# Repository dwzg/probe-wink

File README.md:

# probe-wink

Wink and alternation mod for the pop-up headlamps of the 1989–92 Ford Probe.
Each headlamp gets a small sealed module that plugs in between the factory
retractor plug and the retractor through a Y-adapter. A relay in the module
swaps the retractor's UP and DOWN command lines, so one lamp can go down while
the other stays up (a wink), or the two can flip in turn. With the relay off,
the car behaves exactly as stock. The LH module talks to a phone and a BLE
remote; the RH module follows it over an authenticated ESP-NOW link. Power
comes from the retractor's own feed; no wires go into the cabin.

## Status

| Part              | State                                                   |
|-------------------|---------------------------------------------------------|
| PCB (rev C)       | designed, ERC/DRC and layout checks pass; not yet built |
| Housing (rev C)   | designed and checked on the model; not yet printed      |
| Firmware          | logic unit-tested on the host; runs on an ESP32 devkit (boot, radio, BLE, phone pairing); not yet run on the module |
| Android app       | built with home-screen widgets; unit tests and lint pass; not yet run on a phone |
| On the car        | nothing tested yet                                      |

## How it works, in short

Both retractors hang on the same two command wires from the headlamp switch.
That is why the lamps always move together. Crossing the two wires for one
retractor sends that lamp the opposite way. Details:
[docs/how-it-works.md](docs/how-it-works.md).

## Documentation

- [How it works](docs/how-it-works.md)
- [Installation](docs/installation.md)
- [Using it](docs/using.md)
- [Building](docs/building.md)
- [Testing](docs/testing.md)
- [Design notes](docs/design-notes.md)

## Repository

| Path            | Contents                                                     |
|-----------------|--------------------------------------------------------------|
| `docs/`         | documentation and diagrams                                   |
| `pcb/`          | KiCad project, generated from Python (`schematic.py`, `check.py`, `board.py`, `fab.py`, `export_enclosure.py`); [README](pcb/README.md) |
| `enclosure/`    | 3D-printable housing in build123d (`housing.py`, `check.py`, `render.py`); current STEP/STL in `enclosure/models/` |
| `firmware/`     | Rust on ESP-IDF for the ESP32-C3; [README](firmware/README.md) |
| `android/`      | Android app with home-screen widgets; [README](android/README.md) |
| `tools/hw-design/` | submodule: [hw-design](https://github.com/dwzg/hw-design), the KiCad and build123d library used by `pcb/` and `enclosure/` |
| `Makefile`      | one target per part                                          |

## Quick start

The board and housing generators use the [hw-design](https://github.com/dwzg/hw-design)
library as a submodule. Clone with `git clone --recurse-submodules`, or run
`git submodule update --init` in an existing clone.

```sh
make pcb         # schematic -> ERC/netlist check -> board (route, DRC, layout checks) -> JLCPCB files
make enclosure   # board geometry -> housing STEP/STL -> enclosure checks -> renders
make firmware    # module firmware; needs WINK_BLE_PASSKEY (couple the modules in the app)
make devkit      # the same firmware for an ESP32 DEVKITV1 test bench
make android     # Android app, debug APK
make test        # firmware logic tests + Android unit tests
```

What each target needs (KiCad 10, Freerouting, a Python venv for build123d,
the Rust toolchain): [docs/building.md](docs/building.md).

## Safety

- The module switches the command lines of the headlamp retractors. With the
  relay off, the wiring is stock: at power-up, in reset, in sleep, and without a
  module. Unplugging the Y-adapter restores the original wiring completely.
- Each module's 12 V tap runs through a 1 A fuse in the adapter. Motor power
  never passes through the module.
- The retractor linkage is strong enough to hurt. Disconnect the battery before
  working on it, and keep hands clear whenever it has power.
- Winking or flashing headlamps while driving may be illegal where you live.
  Treat both modes as parked-car features. The modules cannot see whether the
  car is moving.
- This is a hobby project, not yet tested on a car. Use it at your own risk.

## Licence

- **Software** (`firmware/`, `android/`, and the generator scripts in
  `pcb/` and `enclosure/`): [MIT](LICENSE).
- **Hardware design** (the KiCad files in `pcb/`, the housing models built by
  `enclosure/`): [CERN-OHL-P-2.0](LICENSE-HARDWARE), the permissive CERN Open
  Hardware Licence. Source location: <https://github.com/dwzg/probe-wink>.

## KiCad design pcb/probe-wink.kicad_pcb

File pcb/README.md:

# PCB: probe-wink module (rev C)

One module per headlamp. 46 × 40 mm, 2 layers, ESP32-C3-WROOM-02 (or -02U with an
external antenna: same pads) with the antenna overhanging the right edge, TE IM06GR
swap relay, LMR16006X buck from the retractor's own 12 V feed. The module connects
through a 6-wire lead to a Y-adapter between the factory retractor plug and socket;
motor current stays in the adapter.

The KiCad files are **generated**. Edit the Python sources, not the `.kicad_*` files:

| File | Role |
|---|---|
| `schematic.py` | Parts, values, LCSC numbers, nets → `probe-wink.kicad_sch`, `intended_netlist.json` |
| `check.py` | ERC, netlist export, compare against the declared nets |
| `board.py` | Outline, placement, hand-routed power paths, keep-outs, Freerouting, pours, stitching, DRC, layout checks |
| `fab.py` | JLCPCB Gerber/drill zip, BOM, CPL, assembly drawings → `build/fab/` |
| `export_enclosure.py` | Board STEP and geometry JSON for the housing → `../enclosure/build/` |
| `lib/probe-wink.pretty` | Project footprints (back-side pogo pads for J2) |
| `../tools/hw-design/` | Submodule: the generic generator library [hw-design](https://github.com/dwzg/hw-design) (`hwdesign.kicad`) |

## Rebuild

```sh
make pcb                      # from the repository root: the first four steps below

cd pcb
python3 schematic.py          # schematic + lib tables
python3 check.py              # ERC + netlist (board.py reads build/probe-wink.net)
python3 board.py              # about 90 s; add --no-route while iterating on placement
python3 fab.py                # build/fab/
python3 export_enclosure.py   # ../enclosure/build/board.json + probe-wink-board.step
```

Needs KiCad 10 (`pcbnew` Python module, `kicad-cli`), Freerouting on `PATH`,
`rsvg-convert` for the PNG renders.

`board.py` runs the Freerouting strategies in parallel and caches each result
under `build/route-cache/` by a hash of the routing input. A rerun with unchanged
placement (silkscreen, rules) takes about 10 s.

Status at last generation: ERC 0, schematic overlap check 0, netlist matches the
declared nets. DRC 0 errors, 0 unconnected; one warning, the WROOM-02 footprint
differing from the library copy (intentional). 18 of 18 layout checks pass.

## Layout

DRC checks clearances. It does not check whether parts that must be close are close.
`board.py` therefore hand-places and hand-routes the paths that decide whether the
buck and the module behave, and the autorouter only does the rest:

- **Buck** (TI LMR16006 §11.1/11.2): U1 rotated so VIN sits above Cin (C2). The
  catch diode D3 sits beside Cin, so the Cin–switch–diode loop closes on top copper.
  L1 is on the SW side, the output caps are at the L1/D3 junction, and the ground
  ties into the plane at the output caps. The FB divider is at the FB pin, away
  from L1. The back copper under the buck is a solid plane (track keep-out).
- **Module supply:** 100 nF then 10 µF straight above pin 1, fed along the top edge.
  EN jogs left over the unused pins 3/4 to its RC and pull-up.
- **Module body:** no tracks on either layer under the module; GND stitching allowed.
- **Bottom plane:** no tracks under the input stage, FB divider and buck (keep-out
  116–131.6 × 102–122). The FB divider's ground runs on top to the IC ground; its 3V3
  comes from the top-edge rail and crosses under the 12 V link by a 4 mm hop at the edge.
- **Programming:** J2 (EN, 3V3, BOOT, GND) is a 2 × 2 pogo pad set on the back right
  behind the module's top row, so its traces stay local. USB D−/D+ pads are behind the
  bottom row.
- **Harness lines** (HARN_*, RET_*) have their own net class: 0.4 mm, 0.5 mm clearance
  (coupled bursts, no TVS on these lines).
- After routing, extra GND vias go next to the sense and ADC grounds (`via_near`), and
  autorouter leftovers that lead nowhere are removed (`prune_dangling`).
- **Sense buffers:** two compact cells (divider, filter cap, zener on a short gate
  bus, MOSFET, pull-up), placed next to the harness pads.

After routing, `board.py` measures the routed copper between pad pairs
(`hwdesign.kicad.board.path_length`) and fails loudly if a limit is exceeded:

| Path | Rev B | Rev C | Limit |
|---|---|---|---|
| SW: U1 → L1 | 14.7 mm, 2 vias | 6.1 mm | 8 mm, top only |
| SW: U1 → D3 | 11.8 mm, 2 vias | 3.6 mm | 4 mm |
| FB: U1 → R9 | 7.2 mm, 2 vias | 1.7 mm | 3 mm |
| 3V3: module pin 1 → 100 nF | 43.1 mm, 4 vias | 2.6 mm | 4 mm |
| EN: pin 2 → C7 | 16.7 mm, 2 vias | 5.0 mm | 6 mm |
| FB divider GND → IC GND | 27 mm through the planes | 8.8 mm, top | 10 mm |
| Foreign nets in the buck hot loop | 3V3 feed to R9 through it | none | none |

## Circuit notes

- **Swap:** K1 pole 1 (COM 3 / NC 2 / NO 4) feeds the retractor's UP input, pole 2
  (COM 6 / NC 7 / NO 5) its DOWN input. At rest NC passes the stock lines through;
  energized, they cross. Lead wires: 1 harness BK/BL (DOWN), 2 to retractor BK/R,
  3 harness BK/R (UP), 4 to retractor BK/BL, 5 BK/W tap (1 A fuse in the adapter), 6 BK.
- **Input:** M7 reverse diode, SMCJ30A TVS (a load dump ends at the 1 A tap fuse), 22 µF
  bulk electrolytic, 2 × 2.2 µF + 100 nF ceramics.
- **Buck:** LMR16006X at 0.7 MHz, 22 µH (SWPA5040S), PMEG10010ELR catch diode (Schottky
  leakage at 85 °C was the largest sleep load with an SS210), 2 × 10 µF X7R out,
  Vout = 0.765 × (1 + 330k/100k) = 3.29 V.
- **Relay drive:** MMBTA06 NPN with a 2.2k base resistor, about 1.1 mA base drive,
  saturated down to −55 °C (a 2N7002 has no Rds(on) spec at 3.3 V gate drive and may
  not pull the coil in when cold), 100k base pull-down, 1N4148W flyback.
- **Sense:** HARN_UP/HARN_DOWN → 330k/220k divider, 100 nF, 12 V zener → 2N7002 →
  330k pull-up → GPIO0/1, active low, deep-sleep wake. Switching point about
  1.4–7 V on the line.
- **Supply sense:** +12 V → 1 M / 68k → GPIO3 (ADC). The firmware's relay minimum
  follows the die temperature (see [firmware/README.md](../firmware/README.md)).
- **EN:** 10k / 1 µF RC at pin 2 (the C3's brown-out reset covers supply dips).
- **Pins:** GPIO10 relay, GPIO7 LED, GPIO6 side jumper; GPIO4/5 and UART0 (GPIO20/21)
  unused (console on native USB).
- **Programming:** native USB (D−/D+ on the back-side pads TP1/TP2, 3V3 and GND on
  TP3/TP5). ROM download mode works over USB; to force it, hold BOOT low on J2 and
  pulse EN. J2.2 is 3V3 only: never feed it 5 V.
- **Side select:** JP1 (back side) open = LH/master, bridged = RH/slave.

## Assembly

- JLCPCB assembles every part with `Assembly = SMT` (45 placements, 26 BOM lines),
  top side only. All LCSC numbers were checked in stock on 2026-11-01.
- Hand-soldered: the 6-wire lead into J1: sheathed 6 × 0.5 mm² cable (e.g. LiYY 6×0.5,
  about 6.2 mm OD, fits the housing's M12 gland), 1.15 mm holes. The lines carry signal
  current only; the motor current stays in the Y-adapter.
  JP1 is bridged with solder on the RH module only. The back side has no parts,
  only pads.
- Assembly drawings with every reference: `build/fab/probe-wink-assembly-{top,bottom}.pdf`
  (most references don't fit on the silkscreen).

## Review before ordering

- Check every part's rotation in JLC's placement preview; record corrections in
  `ROT_OFFSET` in `fab.py`. Already corrected: SOT-23 and TSOT-23-6 by 180° (Q1–Q3, U1),
  the relay K1 by 90°.
- The ESP32-C3-WROOM-02-N4 is rated −40…85 °C ambient. The -H4 (105 °C, LCSC
  C2944070) has the same pads but showed 0 stock at JLC; consider it for a hot
  mounting spot.
- Radio: test placement with two dev boards in the car first (see
  [docs/testing.md](../docs/testing.md#radio-in-the-car)).

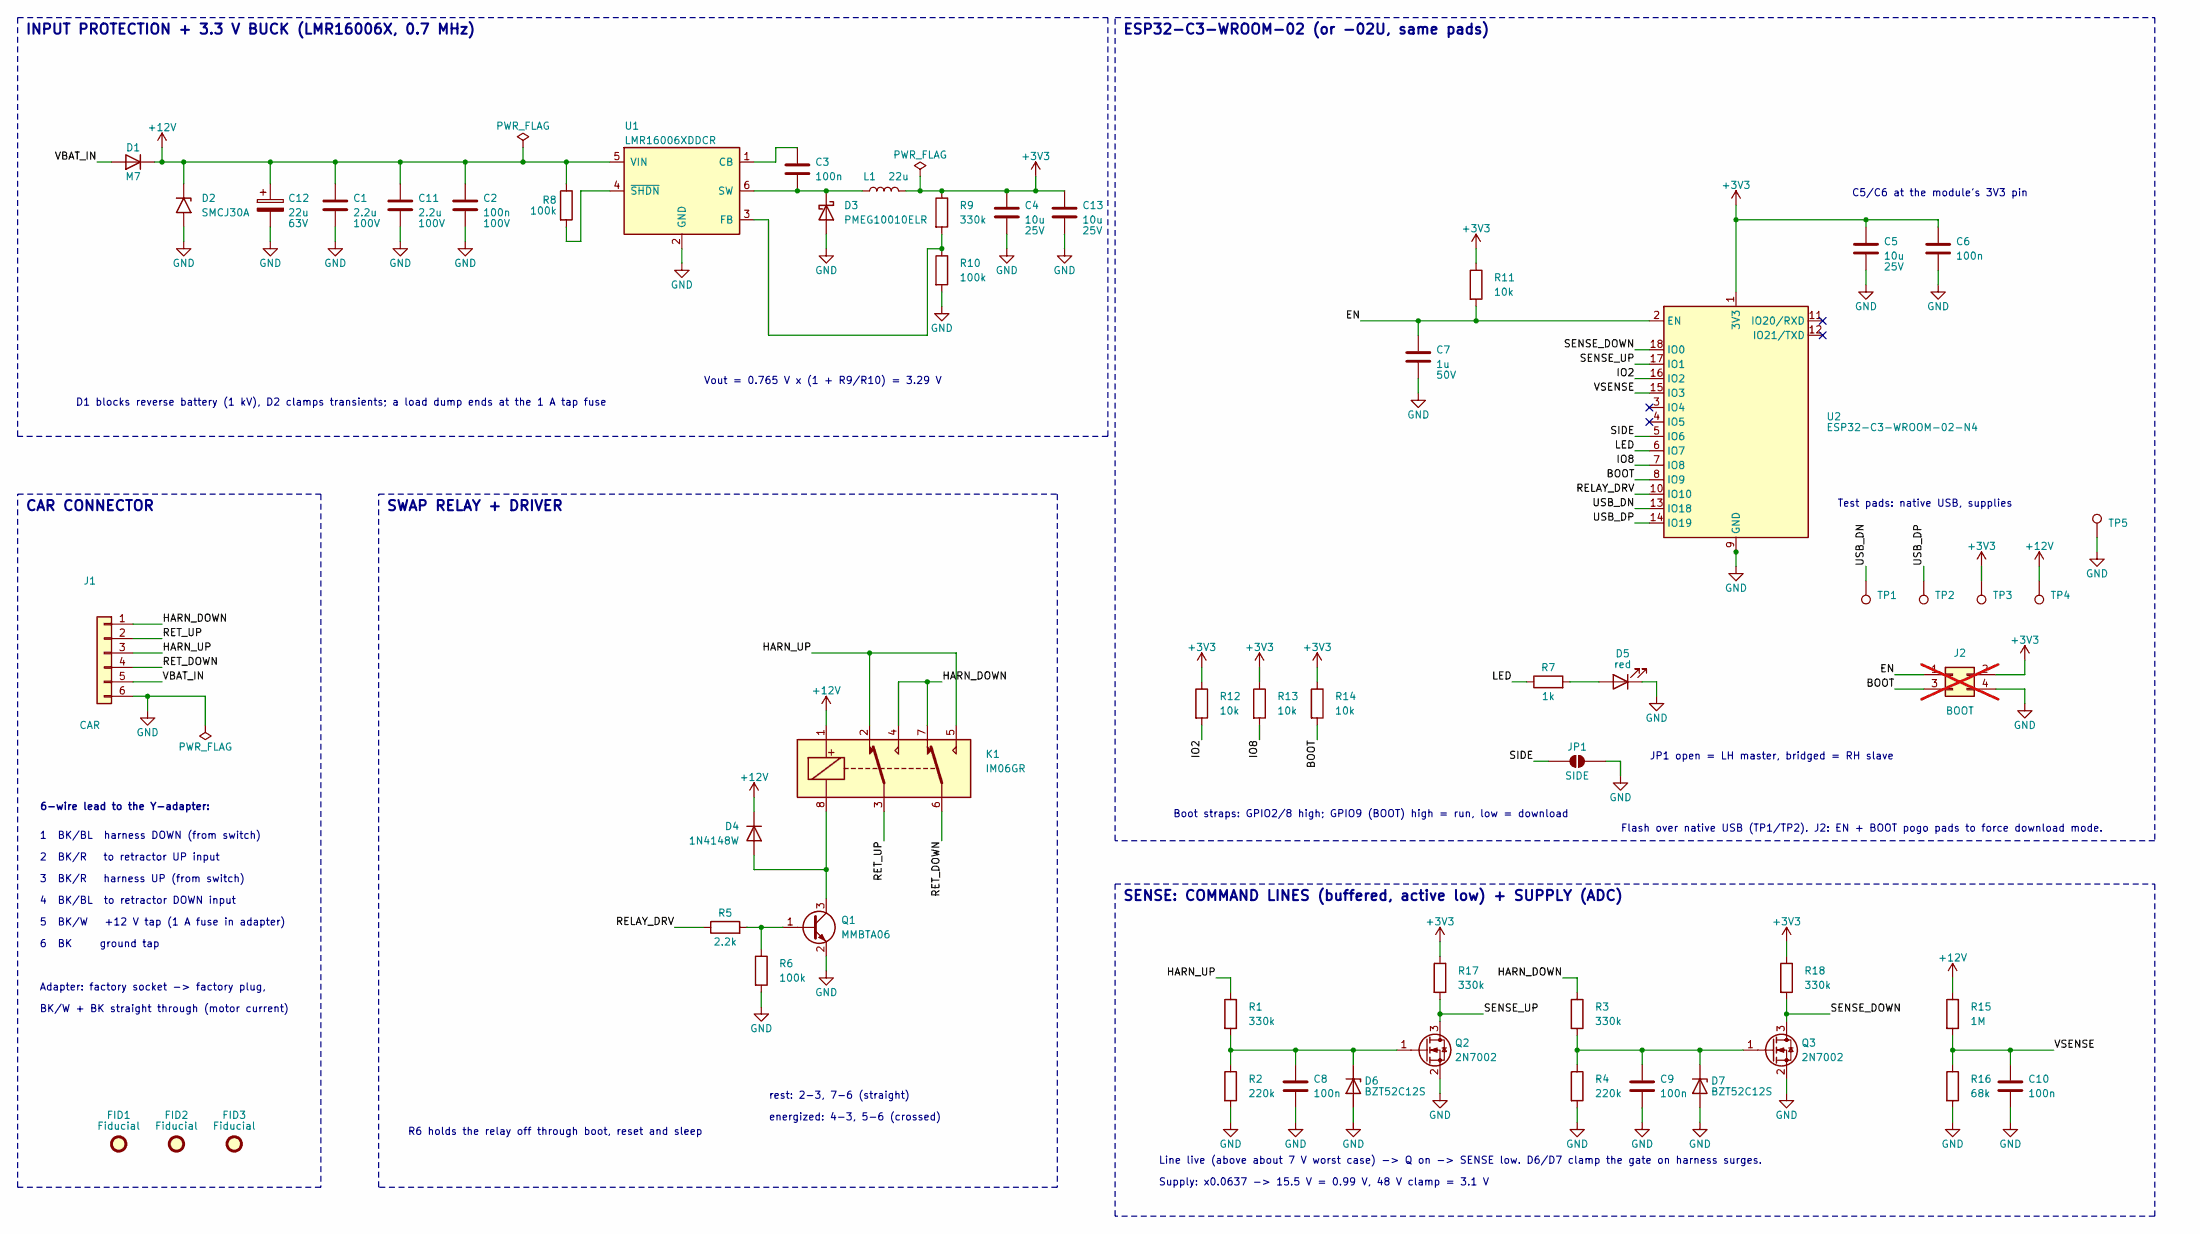
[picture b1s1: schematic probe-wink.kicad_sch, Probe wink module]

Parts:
C1, C11: 2.2u; C_1206_3216Metric; Rating 100V; MPN CC1206KKX7R0BB225; LCSC C577211
C2: 100n; C_0805_2012Metric; Rating 100V; MPN CL21B104KCFNNNE; LCSC C28233
C3, C6, C8, C9, C10: 100n; C_0805_2012Metric; MPN CC0805KRX7R9BB104; LCSC C49678
C4, C5, C13: 10u; C_0805_2012Metric; Rating 25V; MPN CL21B106KAYQNNE; LCSC C3039694
C7: 1u; C_0805_2012Metric; Rating 50V; MPN CL21B105KBFNNNE; LCSC C28323
C12: 22u; CP_Elec_6.3x5.4; Rating 63V; MPN RVT63V22M6X5; LCSC C51018397
D1: M7; D_SMA; MPN M7; LCSC C95872
D2: SMCJ30A; D_SMC; MPN SMCJ30A (Littelfuse); LCSC C224048
D3: PMEG10010ELR; Nexperia_CFP3_SOD-123W; MPN PMEG10010ELRX; LCSC C179426
D4: 1N4148W; D_SOD-123; MPN 1N4148W; LCSC C81598
D5: red; LED_0805_2012Metric; MPN NCD0805R1; LCSC C84256
D6, D7: BZT52C12S; D_SOD-323; MPN BZT52C12S; LCSC C14643
FID1, FID2, FID3: Fiducial; Fiducial_1mm_Mask2mm
J1: CAR; SolderWire-0.5sqmm_1x06_P4.8mm_D0.9mm_OD2.3mm; MPN sheathed 6 x 0.5 mm2 lead (LiYY 6x0.5)
J2: BOOT; PogoPads_2x02_P2.54mm; MPN bare pads on the back behind the module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; not fitted
JP1: SIDE; SolderJumper-2_P1.3mm_Open_RoundedPad1.0x1.5mm
K1: IM06GR; Relay_2P2T_10x6mm_TE_IMxxG; MPN IM06GR (TE), alt HFD4/12-SR C44212; LCSC C2153106
L1: 22u; L_Sunlord_SWPA5040S; MPN SWPA5040S220MT; LCSC C68434
Q1: MMBTA06; SOT-23; MPN MMBTA06LT1G (80 V NPN); LCSC C77760
Q2, Q3: 2N7002; SOT-23; MPN 2N7002; LCSC C8545
R1, R3, R9, R17, R18: 330k; R_0805_2012Metric; MPN 0805W8F3303T5E; LCSC C17629
R2, R4: 220k; R_0805_2012Metric; MPN 0805W8F2203T5E; LCSC C17556
R5: 2.2k; R_0805_2012Metric; MPN 0805W8F2201T5E; LCSC C17520
R6, R8, R10: 100k; R_0805_2012Metric; MPN 0805W8F1003T5E; LCSC C149504
R7: 1k; R_0805_2012Metric; MPN 0805W8F1001T5E; LCSC C17513
R11, R12, R13, R14: 10k; R_0805_2012Metric; MPN 0805W8F1002T5E; LCSC C17414
R15: 1M; R_0805_2012Metric; MPN 0805W8F1004T5E; LCSC C17514
R16: 68k; R_0805_2012Metric; MPN 0805W8F6802T5E; LCSC C17801
TP1: USB_DN; TestPoint_Pad_D1.5mm
TP2: USB_DP; TestPoint_Pad_D1.5mm
TP3: +3V3; TestPoint_Pad_D1.5mm
TP4: +12V; TestPoint_Pad_D1.5mm
TP5: GND; TestPoint_Pad_D1.5mm
U1: LMR16006XDDCR; TSOT-23-6; MPN LMR16006XDDCR; LCSC C87080
U2: ESP32-C3-WROOM-02-N4; ESP32-C3-WROOM-02; MPN ESP32-C3-WROOM-02-N4; LCSC C2934560

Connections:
+3V3: C4.1, C5.1, C6.1, C13.1, J2.2, L1.2, R9.1, R11.1, R12.1, R13.1, R14.1, R17.1, R18.1, TP3.1, U2.1 (3V3)
+12V: C1.1, C2.1, C11.1, C12.1, D1.1 (K), D2.1 (A1), D4.1 (K), K1.1, R8.1, R15.1, TP4.1, U1.5 (VIN)
/BOOT: J2.3, R14.2, U2.8 (IO9)
/EN: C7.1, J2.1, R11.2, U2.2 (EN)
/HARN_DOWN: J1.1, K1.4, K1.7, R3.1
/HARN_UP: J1.3, K1.2, K1.5, R1.1
/IO2: R12.2, U2.16 (IO2)
/IO8: R13.2, U2.7 (IO8)
/LED: R7.1, U2.6 (IO7)
/RELAY_DRV: R5.1, U2.10 (IO10)
/RET_DOWN: J1.4, K1.6
/RET_UP: J1.2, K1.3
/SENSE_DOWN: Q3.3 (D), R18.2, U2.18 (IO0)
/SENSE_UP: Q2.3 (D), R17.2, U2.17 (IO1)
/SIDE: JP1.1 (A), U2.5 (IO6)
/USB_DN: TP1.1, U2.13 (IO18)
/USB_DP: TP2.1, U2.14 (IO19)
/VBAT_IN: D1.2 (A), J1.5
/VSENSE: C10.1, R15.2, R16.1, U2.15 (IO3)
GND: C1.2, C2.2, C4.2, C5.2, C6.2, C7.2, C8.2, C9.2, C10.2, C11.2, C12.2, C13.2, D2.2 (A2), D3.2 (A), D5.1 (K), D6.2 (A), D7.2 (A), J1.6, J2.4, JP1.2 (B), Q1.2 (E), Q2.2 (S), Q3.2 (S), R2.2, R4.2, R6.2, R10.2, R16.2, TP5.1, U1.2 (GND), U2.9 (GND), U2.19 (GND)
unnamed: C3.2, D3.1 (K), L1.1, U1.6 (SW)
unnamed: D4.2 (A), K1.8, Q1.3 (C)
unnamed: D5.2 (A), R7.2
unnamed: C8.1, D6.1 (K), Q2.1 (G), R1.2, R2.1
unnamed: C9.1, D7.1 (K), Q3.1 (G), R3.2, R4.1
unnamed: Q1.1 (B), R5.2, R6.1
unnamed: C3.1, U1.1 (CB)
unnamed: R9.2, R10.1, U1.3 (FB)
unnamed: R8.2, U1.4 (~SHDN)

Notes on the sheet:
INPUT PROTECTION + 3.3 V BUCK (LMR16006X, 0.7 MHz)
Vout = 0.765 V x (1 + R9/R10) = 3.29 V
D1 blocks reverse battery (1 kV), D2 clamps transients; a load dump ends at the 1 A tap fuse
CAR CONNECTOR
6-wire lead to the Y-adapter:
1 BK/BL harness DOWN (from switch)
2 BK/R to retractor UP input
3 BK/R harness UP (from switch)
4 BK/BL to retractor DOWN input
5 BK/W +12 V tap (1 A fuse in adapter)
6 BK ground tap
Adapter: factory socket -> factory plug,
BK/W + BK straight through (motor current)
SWAP RELAY + DRIVER
rest: 2-3, 7-6 (straight)
energized: 4-3, 5-6 (crossed)
R6 holds the relay off through boot, reset and sleep
ESP32-C3-WROOM-02 (or -02U, same pads)
C5/C6 at the module's 3V3 pin
Boot straps: GPIO2/8 high; GPIO9 (BOOT) high = run, low = download
JP1 open = LH master, bridged = RH slave
Test pads: native USB, supplies
Flash over native USB (TP1/TP2). J2: EN + BOOT pogo pads to force download mode.
SENSE: COMMAND LINES (buffered, active low) + SUPPLY (ADC)
Line live (above about 7 V worst case) -> Q on -> SENSE low. D6/D7 clamp the gate on harness surges.
Supply: x0.0637 -> 15.5 V = 0.99 V, 48 V clamp = 3.1 V

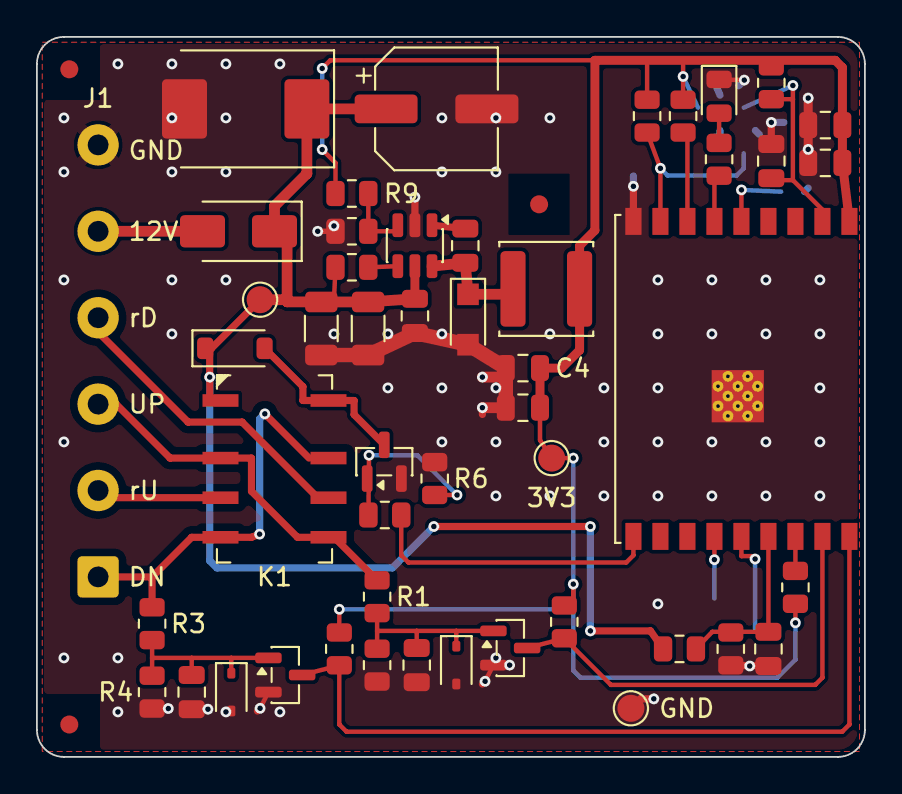
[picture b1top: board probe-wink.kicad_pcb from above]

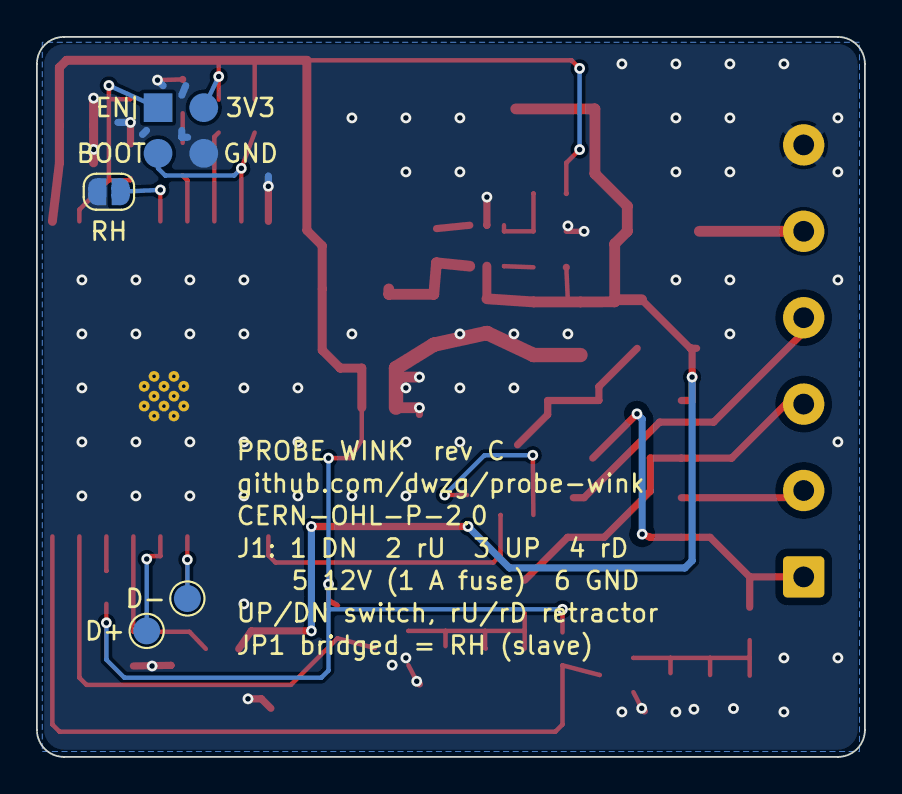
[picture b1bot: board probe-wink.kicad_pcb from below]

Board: 2 copper layers, 46.0 x 40.0 mm, 56 parts (4 on the bottom side), 29 nets.

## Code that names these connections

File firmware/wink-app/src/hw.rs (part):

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
#[cfg(not(esp32))]
mod pins {
    pub const SENSE_UP: u8 = 1;
    pub const SENSE_DOWN: u8 = 0;
    pub const RELAY: i32 = 10;
    pub const VSENSE: Option<i32> = Some(3);
    /// Module pins 3 and 4 (GPIO4, GPIO5) are not connected on rev C.
    pub const UNUSED: &[i32] = &[4, 5];
    /// The board has external pull-ups on the sense lines.
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
#[cfg(esp32)]
mod pins {
    pub const SENSE_UP: u8 = 32;
    pub const SENSE_DOWN: u8 = 33;
    pub const RELAY: i32 = 2;
    pub const VSENSE: Option<i32> = None;
    pub const UNUSED: &[i32] = &[];
    /// Nothing on the devkit's pins: internal pull-ups, a jumper to GND = live.
    pub const SENSE_PULL: super::Pull = super::Pull::Up;
}

pub const PIN_SENSE_UP: u8 = pins::SENSE_UP;
pub const PIN_SENSE_DOWN: u8 = pins::SENSE_DOWN;
pub const PIN_RELAY: i32 = pins::RELAY;
pub const PIN_VSENSE: Option<i32> = pins::VSENSE;
pub const PINS_UNUSED: &[i32] = pins::UNUSED;
/// Re-read the die temperature at most this often.
#[cfg(esp_idf_soc_temp_sensor_supported)]
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            sys::gpio_hold_dis(pin);
            sys::gpio_reset_pin(pin);
        }
        if let Some(pin) = PIN_VSENSE {
            sys::gpio_hold_dis(pin);
        }
    }
}

/// Read the side jumper once at boot.
pub fn read_side(pin: AnyIOPin<'static>) -> Result<Side, EspError> {
    let p = PinDriver::input(pin, Pull::Up)?;
    esp_idf_svc::hal::delay::Ets::delay_us(200);
    let side = if p.is_high() { Side::Lh } else { Side::Rh };
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pub struct Board {
    relay: PinDriver<'static, Output>,
    led: PinDriver<'static, Output>,
    sense_up: PinDriver<'static, Input>,
    sense_down: PinDriver<'static, Input>,
    #[cfg(not(esp32))]
    supply: supply::Adc,
    relay_on: bool,
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
impl Board {
    pub fn new(
        sense_up: AnyIOPin<'static>,
        sense_down: AnyIOPin<'static>,
        relay: AnyIOPin<'static>,
        led: AnyIOPin<'static>,
        supply_pins: SupplyPins,
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        relay.set_low()?;
        let mut led = PinDriver::output(led)?;
        led.set_low()?;
        let sense_up = PinDriver::input(sense_up, pins::SENSE_PULL)?;
        let sense_down = PinDriver::input(sense_down, pins::SENSE_PULL)?;
        #[cfg(not(esp32))]
        let supply = supply::new(supply_pins.0, supply_pins.1)?;
        #[cfg(esp32)]
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        let _ = if on { self.led.set_high() } else { self.led.set_low() };
    }

    /// Raw pin levels (SENSE_UP high, SENSE_DOWN high). Active low: a live
    /// harness line reads LOW; see `config::SENSE_POLARITY`.
    pub fn sense_pins(&self) -> (bool, bool) {
        (self.sense_up.is_high(), self.sense_down.is_high())
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

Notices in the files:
pcb/probe-wink.kicad_sch:
CERN-OHL-P-2.0 - source: github.com/dwzg/probe-wink
